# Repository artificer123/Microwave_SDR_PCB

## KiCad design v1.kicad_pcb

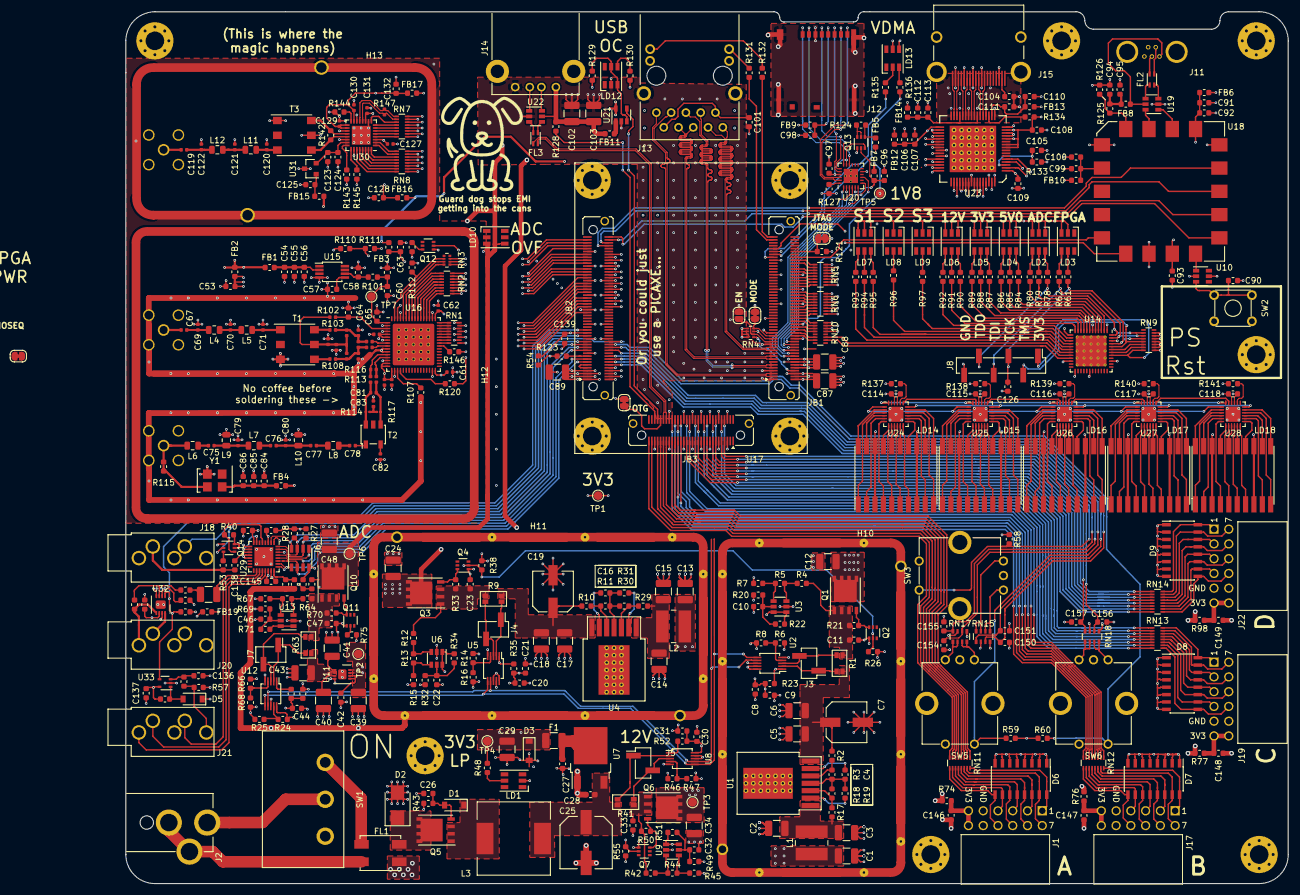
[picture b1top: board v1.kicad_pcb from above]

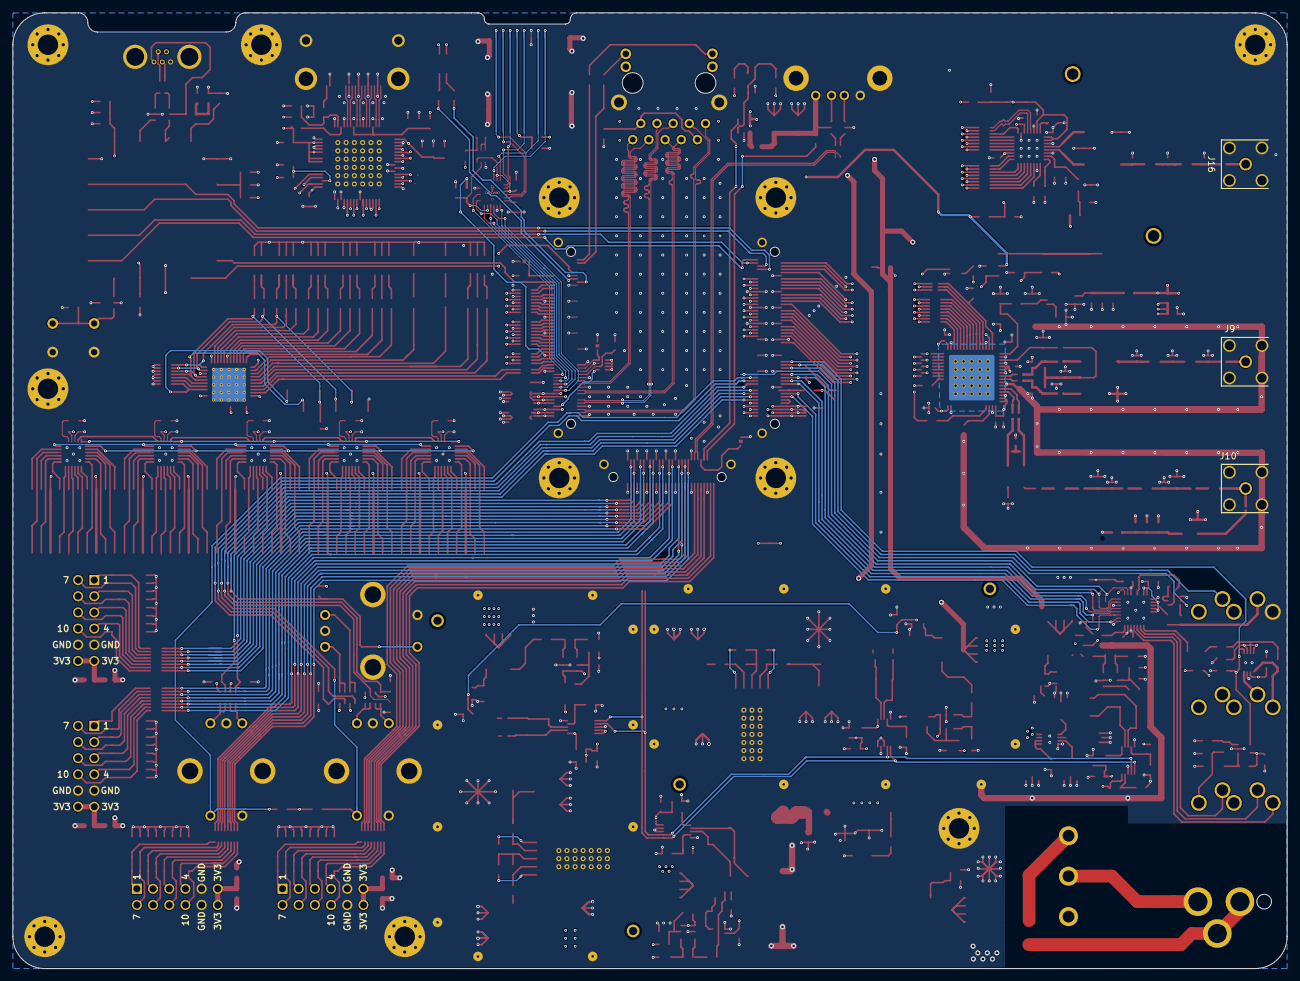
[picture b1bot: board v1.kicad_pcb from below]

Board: 4 copper layers, 200.0 x 150.0 mm, 468 parts (3 on the bottom side), 578 nets.

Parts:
C1, C2, C3, C13, C14, C15: 10u; C_1210_3225Metric
C4, C16: 470n; C_0603_1608Metric
C5, C6, C12, C17, C18, C24, C29, C34, C39, C40, C41, C43, C48, C87, C88, C89, C133: 22u; C_1210_3225Metric
C7, C19: 220u; Wurth_WCAP_PSLP
C8, C11, C20, C23, C27, C28, C30, C33, C44, C47, C136: 4u7; C_0603_1608Metric
C9, C10, C21, C22, C31, C32, C45, C46, C55, C60, C85, C90, C92, C93, C95, C100, C101, C105, C107, C108, C109, C111, C113, C114, C115, C116, C117, C118, C124, C125, C137, C139, C141, C144, C145: 100n; C_0603_1608Metric
C25: 220u; Wurth_WCAP_PSHP
C26: 47n; C_0603_1608Metric
C42, C53, C57, C63, C91, C94, C99, C123, C128, C132, C134, C142, C143, C146, C147, C148, C149, C158: 1u; C_0603_1608Metric
C50, C51, C52, C61, C62, C67, C73, C78, C82, C83, C119, C127, C129, C130, C131: 100n; C_0402_1005Metric
C54, C58, C59, C84, C106, C110, C112, C138, C140: 10u; C_0603_1608Metric
C56, C65, C86: 1n; C_0603_1608Metric
C64: 2u2; C_0603_1608Metric
C66, C72, C74, C76, C81: 8p2; C_0402_1005Metric
C68: 10n; C_0402_1005Metric
C69, C71, C120, C122: 47p; C_0402_1005Metric
C70, C121: 150p; C_0402_1005Metric
C75, C77: 22p; C_0402_1005Metric
C79, C80: 200p; C_0402_1005Metric
C96, C97, C98, C104: 100nF; C_0603_1608Metric
C102, C103: 47u; C_1210_3225Metric
C126: 22p; C_0603_1608Metric
C150, C151, C154, C155, C156, C157: 10n; C_0603_1608Metric
D1: MM3Z15VT1G; D_SOD-123
D2: SMAJ24A; D_SMB
D3: MMSZ5V1T1G; D_SOD-123
D5: MBR0520LT1G; D_SOD-123
D6, D7, D8, D9: S16C03-8; SOIC-16_3.9x9.9mm_P1.27mm
F1: 150mA; R_1210_3225Metric
FB1, FB2, FB3, FB4, FB15, FB16, FB17, FB18, FB19: Ferrite_Bead_Small; R_0603_1608Metric
FB5, FB6, FB7, FB8, FB9, FB10, FB11: Ferrite_Bead; R_0603_1608Metric
FB12, FB13, FB14: BLM18RK601SN1D; R_0603_1608Metric
FL1: ACM7060-301-2PL-TL01; TDK_ACM7060-301-2PL-TL01
FL2, FL3: 744231091; Wurth_CM_USB_744231091
H1, H2, H3, H4, H5, H6, H9: MountingHole_Pad; MountingHole_3.2mm_M3_Pad_Via
H10, H11: Shield; Shield_Masach_MS570-10_52.7x30.7x6mm_TH
H12: Shield; Shield_Masach_MS585-10_58.2x49.4x4.7mm_SMD
H13: Shield; Shield_Masach_MS511-10_51.1x25.7x6.5mm_TH
J1, J17, J19, J22: Connector_PMOD_2x6_Host; PMOD_Wurth_613012243121_Horizontal_Host
J2: Barrel_Jack_Switch; Barrel-Jack_Cliff_FC681478_TH
J3, J4, J5, J7: Conn_01x02; PinHeader_1x02_P2.54mm_Vertical_SMD_Pin1Left
J6: CLM-104-02-F-D; Header_Samtec_CLM-104-02-F-D_2x4_1mm_SM
J8: Conn_01x06_Male; PinHeader_1x06_P2.54mm_Vertical_SMD_Pin1Left
J9, J10, J16: Conn_Coaxial; SMA_Linx_CONSMA002-L-G_Horizontal
J11: USB_B_Micro; Micro-USB_Amphenol_MUSB-K152-30_Horizontal_TH
J12: Micro_SD_Card_Det; Micro-SD_Molex_503398-1892
J13: ARJM11D7-502-AB-EW2; Connector_RJ45_Magjack_Abracon_ARJM11D7-502-AB-EW2
J14: USB_A; USB-A_Wurth_61400416021_TH_RA
J15: HDMI_A; HDMI_Wurth_685119134923_Horizontal
J18: SJ1-3535NG-PI; Jack_3.5mm_CUI_SJ1-3535NG-PI_Horizontal_CircularHoles_Pink
J20, J21: SJ1-3535NG-GR; Jack_3.5mm_CUI_SJ1-3535NG-GR_Horizontal_CircularHoles_Green
JP1, JP2, JP4, JP5: SolderJumper_2_Bridged; SolderJumper-2_P1.3mm_Bridged_RoundedPad1.0x1.5mm
JP3: SolderJumper_2_Open; SolderJumper-2_P1.3mm_Open_RoundedPad1.0x1.5mm
L1, L2: 2u2; L_Wuerth_WE-PD2-Typ-MS
L3: 100uH; Wurth_7447709101
L4, L5, L11, L12: 330n; L_0805_2012Metric
L6, L8: 220n; L_0805_2012Metric
L7: 560n; L_0805_2012Metric
L9, L10: 24n; L_0805_2012Metric
LD1, LD2, LD3, LD4, LD5, LD6, LD7, LD8, LD9, LD10, LD12, LD13: LED_Cree_CLX6E-FKC; LED_RGB_PLCC-6
LD14, LD15, LD16, LD17, LD18: ACDA02-41SURKWA-F01
M1: Logo_16mmx16mm
Q1, Q3, Q5, Q6, Q10: Si7141DP; PowerPAK_SO-8_Single
Q2, Q4, Q7, Q11, Q12, Q13, Q14: SI1539CDL-T1-GE3; SOT-363_SC-70-6
R1, R9, R41: 10m; R_Shunt_Vishay_WSK1206
R2, R18, R21, R24, R26, R30, R33, R36, R37, R38, R39, R40, R43, R50, R54, R55, R57, R70, R73, R75, R101, R111, R112, R123, R124, R126, R128, R144, R145: 10k; R_0603_1608Metric
R3: 3k16; R_0603_1608Metric
R4, R64: 330k; R_0603_1608Metric
R5, R65: 2k74; R_0603_1608Metric
R6, R14, R45, R46, R48, R61, R66, R79, R85, R88, R91, R94, R96, R97, R121, R129, R135: 33k; R_0603_1608Metric
R7, R67: 44k2; R_0603_1608Metric
R8, R16, R131, R132: 1k; R_0603_1608Metric
R10: 36k; R_0603_1608Metric
R11: 6k8; R_0603_1608Metric
R12: 430k; R_0603_1608Metric
R13: 2k26; R_0603_1608Metric
R15: 36k5; R_0603_1608Metric
R17, R29: 68k; R_0603_1608Metric
R19, R31: 0R; R_0603_1608Metric
R20, R32, R49, R69: 100R; R_0603_1608Metric
R22, R23, R34, R35, R51, R52, R71, R72: 47k; R_0603_1608Metric
R25, R62, R80, R86, R89, R92, R93, R119, R130, R136, R137, R138, R139, R140, R141: 22k; R_0603_1608Metric
R27, R28: 2k2; R_0603_1608Metric
R42: 1M2; R_0603_1608Metric
R44: 12k; R_0603_1608Metric
R47: 470; R_0603_1608Metric
R53, R143: 2k; R_0603_1608Metric
R56: 100k; R_0603_1608Metric
R58, R59, R60: 10K; R_0603_1608Metric
R63: 50m; R_Shunt_Vishay_WSK1206
R68: 680; R_0603_1608Metric
R74, R76, R77, R98: 10; R_0603_1608Metric
R78, R84, R87, R90, R95: 7k5; R_0603_1608Metric
R102, R104, R109, R113, R118: 5R1; R_0402_1005Metric
R103, R108: 10R; R_0402_1005Metric
R105, R106: 35R; R_0402_1005Metric
R107, R115, R127, R133: 0; R_0603_1608Metric
R110: 5k1; R_0603_1608Metric
R114, R117: 51R; R_0201_0603Metric
R116: 100R; R_0402_1005Metric
R120, R146: 33; R_0603_1608Metric
R125: 4k7; R_0603_1608Metric
R134: 510; R_0603_1608Metric
R142: DNF; R_0603_1608Metric
R147: 1k; R_0402_1005Metric
RN1, RN2, RN5, RN6, RN10: 33; R_Array_Convex_8x0602
RN3: 33; R_Array_Convex_4x0402
RN4: 33k; R_Array_Concave_4x0402
RN7, RN8, RN11, RN12, RN13, RN14: R_Pack08; R_Array_Convex_8x0602
RN9: 5k1; R_Array_Convex_8x0602
RN15, RN17, RN18: 10k; R_Array_Convex_4x0603
SW1: SW_SPDT; C+K_Slide_SPDT_S102031MS02Q_TH
SW2: Tactile_Switch_Generic; SW_TH_Tactile_Omron_B3F-10xx
SW3, SW5, SW6: Rotary_Encoder_Switch; Bourns_QuadratureEncoder_PEC11R-4015K-S0024
T1, T3: PWB2010L; Coilcraft_PWB
T2: Macom_ETC1-1-13; Transformer_MACOM_SM-22
TP1: 3V3; TestPoint_Pad_D1.5mm
TP2: 5V0; TestPoint_Pad_D1.5mm
TP3: V In; TestPoint_Pad_D1.5mm
TP4: 3V3 LP; TestPoint_Pad_D1.5mm
TP5: 1V8; TestPoint_Pad_D1.5mm
TP6: 3V3_ADC; TestPoint_Pad_D1.5mm
TP7: TestPoint; TestPoint_Pad_D1.5mm
U1, U4: 171050601; Wurth_171050601_TO263-7EP_EP6.4x8.54mm
U2, U5, U8, U12: MAX9612; uMAX-10_3x3mm_P0.5mm
U3, U6, U9, U13: TPS3701DDCR; SOT-23-6
U7: NCP1117-3.3_TO252; TO-252-2
U10, U19, U22: TPD2S017; SOT-23-6
U11: ADM7154; LFCSP-8-1EP_3x3mm_P0.5mm_EP1.45x1.74mm
U14: LCMXO2-640HC-4SG48C; QFN-48-1EP_7x7mm_P0.5mm_EP5.3x5.3mm_ThermalVias
U15: REF5025IDGK; MSOP-8_3x3mm_P0.65mm
U16: LTC2216; QFN-64-1EP_9x9mm_P0.5mm_EP7.15x7.15mm
U17: TE0720; Trenz_TE0720
U18: JTAG-SMT3; JTAG-SMT3-NC
U20: TXS02612; WQFN-24-1EP_4.1x4.1mm_P0.5mm_EP2.45x2.45mm
U21: TPS2051B; SOT-23-5
U23: TFP410PAP; TQFP-64-1EP_10x10mm_P0.5mm_EP5x5mm_ThermalVias
U24, U25, U26, U27, U28: TLC59281RGER; QFN-24-1EP_4x4mm_P0.5mm_EP2.6x2.6mm
U29: ADAU1361; LFCSP-32-1EP_5x5mm_P0.5mm_EP3.25x3.25mm
U30: AD9744_LFCSP; LFCSP-32-1EP_5x5mm_P0.5mm_EP3.25x3.25mm
U31: ADR280RT; SOT-23
U32: SSM2211; LFCSP-8-1EP_3x3mm_P0.5mm_EP1.45x1.74mm
U33: TLV7031DCK; SOT-353_SC-70-5
Y1: SIT5001AC-3E-33N0-80.000000X; TCXO_Sitime_SiT5001_5x3.2mm

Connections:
1V8_from_FPGA: FB7.1, TP5.1, U17.1.40
3V3ADC_I_Good: R72.2, U12.1, U14.33
3V3ADC_V_Good: R71.2, U13.1, U13.6, U14.34
3V3_I_Good: R23.2, U2.1, U14.26
3V3_LP: C8.1, C9.1, C20.1, C21.1, C29.1, C30.1, C31.1, C44.1, C45.1, D3.1, F1.1, R6.1, R14.1, R20.2, R23.1, R24.1, R32.2, R35.1, R46.1, R48.1, R49.2, R52.1, R66.1, R69.2, R72.1, RN9.10, RN9.11, RN9.12, RN9.14, RN9.15, TP4.1, U2.9, U2.10, U5.8, U5.10, U8.10, U12.10, U14.1, U14.6, U14.13, U14.22, U14.25, U14.30, U14.39, U14.46
3V3_V_Good: R22.2, U3.1, U3.6, U14.27
5V_I_Good: R35.2, U5.1, U14.28
5V_V_Good: R34.2, U6.1, U6.6, U14.29
12V_I_Good: R52.2, U8.1, U14.23
12V_V_Good: R51.2, U9.1, U9.6, U14.24
+3.3VADC: C48.1, FB1.2, FB2.1, FB15.1, FB17.1, FB18.1, FB19.1, LD10.4, Q10.5, TP6.1
+3V3: C12.1, C87.1, C88.1, C89.1, C114.1, C115.1, C116.1, C117.1, C118.1, C137.1, C142.1, FB3.1, FB5.1, FB6.1, FB9.1, FB10.1, FB12.2, FB13.2, FB14.2, FB16.1, J13.L1, J13.L3, LD13.4, LD13.5, LD14.3, LD14.8, LD14.13, LD14.18, LD15.3, LD15.8, LD15.13, LD15.18, LD16.3, LD16.8, LD16.13, LD16.18, LD17.3, LD17.8, LD17.13, LD17.18, LD18.3, LD18.8, LD18.13, LD18.18, Q1.5, R27.1, R28.1, R54.1, R58.1, R59.1, R60.1, R73.1, R74.2, R76.2, R77.2, R98.2, R121.1, R123.1, R129.1, R130.1, RN4.5, RN4.6, RN4.7, RN4.8, RN15.2, RN15.4, RN17.1, RN17.3, RN18.1, RN18.3, TP1.1, U10.5, U17.1.2, U17.1.4, U17.1.6, U17.1.10, U17.1.12, U17.1.14, U17.1.16, U17.2.1, U17.2.2, U17.2.3, U17.2.4, U17.2.5, U17.2.6, U17.2.7, U17.2.8, U17.2.10, U24.21, U25.21, U26.21, U27.21, U28.21, U29.1, U33.5
+5V: C24.1, C39.1, Q3.5, TP2.1, U11.7, U11.8, U21.5
/AF ADC/DAC/CM: U29.7, U29.10, U29.12, U29.13
/FPGA/Connectors/D+: J14.3, U22.1
/FPGA/Connectors/D-: J14.2, U22.6
/FPGA/Connectors/USB_DBG_D+: U18.17, U19.6
/FPGA/Connectors/USB_DBG_D-: U18.16, U19.1
/FPGA/Connectors/~USB_OC: LD12.3, LD12.5, R129.2, U21.3
/FPGA/JB1/EN1: JP3.1, RN4.2, U17.1.27
/FPGA/JB1/JTAGMODE: JP1.1, R121.2, U17.1.90
/FPGA/JB1/MODE: JP4.1, RN4.4, U17.1.31
/FPGA/JB1/NOSEQ: JP2.1, RN4.1, U17.1.8
/FPGA/PMOD Connectors/PMOD A/1: D6.16, J1.1, RN11.16
/FPGA/PMOD Connectors/PMOD A/2: D6.14, J1.2, RN11.14
/FPGA/PMOD Connectors/PMOD A/3: D6.12, J1.3, RN11.12
/FPGA/PMOD Connectors/PMOD A/4: D6.10, J1.4, RN11.10
/FPGA/PMOD Connectors/PMOD A/7: D6.15, J1.7, RN11.15
/FPGA/PMOD Connectors/PMOD A/8: D6.13, J1.8, RN11.13
/FPGA/PMOD Connectors/PMOD A/9: D6.11, J1.9, RN11.11
/FPGA/PMOD Connectors/PMOD A/10: D6.9, J1.10, RN11.9
/FPGA/PMOD Connectors/PMOD B/1: D7.16, J17.1, RN12.16
/FPGA/PMOD Connectors/PMOD B/2: D7.14, J17.2, RN12.14
/FPGA/PMOD Connectors/PMOD B/3: D7.12, J17.3, RN12.12
/FPGA/PMOD Connectors/PMOD B/4: D7.10, J17.4, RN12.10
/FPGA/PMOD Connectors/PMOD B/7: D7.15, J17.7, RN12.15
/FPGA/PMOD Connectors/PMOD B/8: D7.13, J17.8, RN12.13
/FPGA/PMOD Connectors/PMOD B/9: D7.11, J17.9, RN12.11
/FPGA/PMOD Connectors/PMOD B/10: D7.9, J17.10, RN12.9
/FPGA/PMOD Connectors/PMOD C/1: D8.16, J19.1, RN13.16
/FPGA/PMOD Connectors/PMOD C/2: D8.14, J19.2, RN13.14
/FPGA/PMOD Connectors/PMOD C/3: D8.12, J19.3, RN13.12
/FPGA/PMOD Connectors/PMOD C/4: D8.10, J19.4, RN13.10
/FPGA/PMOD Connectors/PMOD C/7: D8.15, J19.7, RN13.15
/FPGA/PMOD Connectors/PMOD C/8: D8.13, J19.8, RN13.13
/FPGA/PMOD Connectors/PMOD C/9: D8.11, J19.9, RN13.11
/FPGA/PMOD Connectors/PMOD C/10: D8.9, J19.10, RN13.9
/FPGA/PMOD Connectors/PMOD D/1: D9.16, J22.1, RN14.16
/FPGA/PMOD Connectors/PMOD D/2: D9.14, J22.2, RN14.14
/FPGA/PMOD Connectors/PMOD D/3: D9.12, J22.3, RN14.12
/FPGA/PMOD Connectors/PMOD D/4: D9.10, J22.4, RN14.10
/FPGA/PMOD Connectors/PMOD D/7: D9.15, J22.7, RN14.15
/FPGA/PMOD Connectors/PMOD D/8: D9.13, J22.8, RN14.13
/FPGA/PMOD Connectors/PMOD D/9: D9.11, J22.9, RN14.11
/FPGA/PMOD Connectors/PMOD D/10: D9.9, J22.10, RN14.9
/HDMI/Active: RN10.15, U23.2
/HDMI/B0: RN10.16, U23.60
/HDMI/B1: RN6.9, U23.59
/HDMI/B2: RN6.10, U23.58
/HDMI/B3: RN6.12, U23.55
/HDMI/B4: RN6.13, U23.54
/HDMI/CK+: J15.10, U23.22
/HDMI/CK-: J15.12, U23.21
/HDMI/Clk: RN6.11, U23.57
/HDMI/G0: RN6.14, U23.51
/HDMI/G1: RN6.15, U23.50
/HDMI/G2: RN6.16, U23.47
/HDMI/G3: RN5.9, U23.46
/HDMI/G4: RN5.10, U23.45
/HDMI/G5: RN5.11, U23.44
/HDMI/HSync: RN10.14, U23.4
/HDMI/PVDD: C110.1, C111.1, FB13.1, U23.18
/HDMI/R0: RN5.12, U23.40
/HDMI/R1: RN5.13, U23.39
/HDMI/R2: RN5.14, U23.38
/HDMI/R3: RN5.15, U23.37
/HDMI/R4: RN5.16, U23.36
/HDMI/TX0+: J15.7, U23.25
/HDMI/TX0-: J15.9, U23.24
/HDMI/TX1+: J15.4, U23.28
/HDMI/TX1-: J15.6, U23.27
/HDMI/TX2+: J15.1, U23.31
/HDMI/TX2-: J15.3, U23.30
/HDMI/VREF: C105.1, R133.2, U23.3
/HDMI/VSync: RN10.13, U23.5
/Power Supply/Power Rail Management/3V3ADC_IFault: R80.1, U14.3
/Power Supply/Power Rail Management/3V3ADC_OK: R79.1, U14.2
/Power Supply/Power Rail Management/3V3ADC_VFault: J8.5, R78.1, RN9.2, U14.48
/Power Supply/Power Rail Management/3V3_IFault: R89.1, U14.10
/Power Supply/Power Rail Management/3V3_OK: R88.1, U14.9
/Power Supply/Power Rail Management/3V3_VFault: R87.1, U14.8
/Power Supply/Power Rail Management/5V_IFault: R86.1, U14.7
/Power Supply/Power Rail Management/5V_OK: R85.1, U14.5
/Power Supply/Power Rail Management/5V_VFault: R84.1, U14.4
/Power Supply/Power Rail Management/12V_IFault: R92.1, U14.14
/Power Supply/Power Rail Management/12V_OK: R91.1, U14.12
/Power Supply/Power Rail Management/12V_VFault: R90.1, U14.11
/Power Supply/Power Rail Management/FPGA_Fault: J8.4, R62.1, RN9.3, U14.47
/Power Supply/Power Rail Management/FPGA_OK: C126.1, J8.3, R61.1, RN9.4, U14.45
/Power Supply/Power Rail Management/I2C_Error: R93.1, U14.19
/Power Supply/Power Rail Management/JTAGEN: J8.1, RN9.8, U14.41
/Power Supply/Power Rail Management/UART_Error: R95.1, U14.17
/Power Supply/Stage 1 Regulators/12V Monitor/INa: R42.2, R44.1, U9.3
/Power Supply/Stage 1 Regulators/12V Monitor/INb: R44.2, R45.1, U9.4
/Power Supply/Stage 1 Regulators/12V Monitor/Sense+: J5.1, R41.3, U8.2
/Power Supply/Stage 1 Regulators/12V Monitor/Sense-: J5.2, R41.2, U8.3
/Power Supply/Stage 1 Regulators/12V Monitor/SetV: R46.2, R47.1, U8.4
/Power Supply/Stage 1 Regulators/12V Monitor/Vin: C33.1, Q6.1, Q6.2, Q6.3, R41.1, R42.1, R50.1
/Power Supply/Stage 1 Regulators/Vin: D2.1, FL1.2, Q5.5
/Power Supply/Stage 2 Regulators/3V3 Monitor/INa: R4.2, R5.1, U3.3
/Power Supply/Stage 2 Regulators/3V3 Monitor/INb: R5.2, R7.1, U3.4
/Power Supply/Stage 2 Regulators/3V3 Monitor/Sense+: J3.1, R1.3, U2.2
/Power Supply/Stage 2 Regulators/3V3 Monitor/Sense-: J3.2, R1.2, U2.3
/Power Supply/Stage 2 Regulators/3V3 Monitor/SetV: R6.2, R8.1, U2.4
/Power Supply/Stage 2 Regulators/3V3 Monitor/Vin: C11.1, Q1.1, Q1.2, Q1.3, R1.1, R4.1, R21.1
/Power Supply/Stage 2 Regulators/3V3_5A Regulator/FB: R2.2, R3.1, U1.5
/Power Supply/Stage 2 Regulators/3V3_5A Regulator/FB_Gnd: C4.2, R3.2, R18.2, R19.2, U1.4
/Power Supply/Stage 2 Regulators/3V3_5A Regulator/Vout: C5.1, C6.1, C7.1, R1.4, R2.1, U1.7
/Power Supply/Stage 2 Regulators/5V Monitor/INa: R12.2, R13.1, U6.3
/Power Supply/Stage 2 Regulators/5V Monitor/INb: R13.2, R15.1, U6.4
/Power Supply/Stage 2 Regulators/5V Monitor/Sense+: J4.1, R9.3, U5.2
/Power Supply/Stage 2 Regulators/5V Monitor/Sense-: J4.2, R9.2, U5.3
/Power Supply/Stage 2 Regulators/5V Monitor/SetV: R14.2, R16.1, U5.4
/Power Supply/Stage 2 Regulators/5V Monitor/Vin: C23.1, Q3.1, Q3.2, Q3.3, R9.1, R12.1, R33.1
/Power Supply/Stage 2 Regulators/5V_5A Regulator/FB: R10.2, R11.1, U4.5
/Power Supply/Stage 2 Regulators/5V_5A Regulator/FB_Gnd: C16.2, R11.2, R30.2, R31.2, U4.4
/Power Supply/Stage 2 Regulators/5V_5A Regulator/Vout: C17.1, C18.1, C19.1, R9.4, R10.1, U4.7
/Power Supply/Stage 2 Regulators/12V_In: C1.1, C13.1, C34.1, L1.1, L2.1, Q6.5, TP3.1
/Power Supply/Stage 3 Regulators/ADC 3V3 Monitor/A0: R24.2, R25.1, U12.9
/Power Supply/Stage 3 Regulators/ADC 3V3 Monitor/INa: R64.2, R65.1, U13.3
/Power Supply/Stage 3 Regulators/ADC 3V3 Monitor/INb: R65.2, R67.1, U13.4
/Power Supply/Stage 3 Regulators/ADC 3V3 Monitor/Sense+: J7.1, R63.3, U12.2
/Power Supply/Stage 3 Regulators/ADC 3V3 Monitor/Sense-: J7.2, R63.2, U12.3
/Power Supply/Stage 3 Regulators/ADC 3V3 Monitor/SetV: R66.2, R68.1, U12.4
/Power Supply/Stage 3 Regulators/ADC 3V3 Monitor/Vin: C47.1, Q10.1, Q10.2, Q10.3, R63.1, R64.1, R70.1
/RF ADC/ADC_Dither: R120.2, U16.20
/RF DAC/Clk_N: R147.1, RN7.1, U30.13
/RF DAC/Clk_P: R147.2, RN7.2, U30.12
/User Interface/Dual Seven Segment Display 1/D1_A: LD14.17, U24.7
/User Interface/Dual Seven Segment Display 1/D1_B: LD14.16, U24.9
/User Interface/Dual Seven Segment Display 1/D1_C: LD14.4, U24.6
/User Interface/Dual Seven Segment Display 1/D1_D: LD14.2, U24.5
/User Interface/Dual Seven Segment Display 1/D1_DP: LD14.5, U24.8
/User Interface/Dual Seven Segment Display 1/D1_E: LD14.1, U24.3
/User Interface/Dual Seven Segment Display 1/D1_F: LD14.19, U24.4
/User Interface/Dual Seven Segment Display 1/D1_G: LD14.20, U24.2
/User Interface/Dual Seven Segment Display 1/D2_A: LD14.12, U24.15
/User Interface/Dual Seven Segment Display 1/D2_B: LD14.11, U24.17
/User Interface/Dual Seven Segment Display 1/D2_C: LD14.9, U24.14
/User Interface/Dual Seven Segment Display 1/D2_D: LD14.7, U24.12
/User Interface/Dual Seven Segment Display 1/D2_DP: LD14.10, U24.16
/User Interface/Dual Seven Segment Display 1/D2_E: LD14.6, U24.10
/User Interface/Dual Seven Segment Display 1/D2_F: LD14.14, U24.13
/User Interface/Dual Seven Segment Display 1/D2_G: LD14.15, U24.11
/User Interface/Dual Seven Segment Display 2/D1_A: LD15.17, U25.7
/User Interface/Dual Seven Segment Display 2/D1_B: LD15.16, U25.9
/User Interface/Dual Seven Segment Display 2/D1_C: LD15.4, U25.6
/User Interface/Dual Seven Segment Display 2/D1_D: LD15.2, U25.5
/User Interface/Dual Seven Segment Display 2/D1_DP: LD15.5, U25.8
/User Interface/Dual Seven Segment Display 2/D1_E: LD15.1, U25.3
/User Interface/Dual Seven Segment Display 2/D1_F: LD15.19, U25.4
/User Interface/Dual Seven Segment Display 2/D1_G: LD15.20, U25.2
/User Interface/Dual Seven Segment Display 2/D2_A: LD15.12, U25.15
/User Interface/Dual Seven Segment Display 2/D2_B: LD15.11, U25.17
/User Interface/Dual Seven Segment Display 2/D2_C: LD15.9, U25.14
/User Interface/Dual Seven Segment Display 2/D2_D: LD15.7, U25.12
/User Interface/Dual Seven Segment Display 2/D2_DP: LD15.10, U25.16
/User Interface/Dual Seven Segment Display 2/D2_E: LD15.6, U25.10
/User Interface/Dual Seven Segment Display 2/D2_F: LD15.14, U25.13
/User Interface/Dual Seven Segment Display 2/D2_G: LD15.15, U25.11
/User Interface/Dual Seven Segment Display 2/SIN: U24.19, U25.23
/User Interface/Dual Seven Segment Display 3/D1_A: LD16.17, U26.7
/User Interface/Dual Seven Segment Display 3/D1_B: LD16.16, U26.9
/User Interface/Dual Seven Segment Display 3/D1_C: LD16.4, U26.6
/User Interface/Dual Seven Segment Display 3/D1_D: LD16.2, U26.5
/User Interface/Dual Seven Segment Display 3/D1_DP: LD16.5, U26.8
/User Interface/Dual Seven Segment Display 3/D1_E: LD16.1, U26.3
/User Interface/Dual Seven Segment Display 3/D1_F: LD16.19, U26.4
/User Interface/Dual Seven Segment Display 3/D1_G: LD16.20, U26.2
/User Interface/Dual Seven Segment Display 3/D2_A: LD16.12, U26.15
/User Interface/Dual Seven Segment Display 3/D2_B: LD16.11, U26.17
/User Interface/Dual Seven Segment Display 3/D2_C: LD16.9, U26.14
/User Interface/Dual Seven Segment Display 3/D2_D: LD16.7, U26.12
/User Interface/Dual Seven Segment Display 3/D2_DP: LD16.10, U26.16
/User Interface/Dual Seven Segment Display 3/D2_E: LD16.6, U26.10
/User Interface/Dual Seven Segment Display 3/D2_F: LD16.14, U26.13
/User Interface/Dual Seven Segment Display 3/D2_G: LD16.15, U26.11
/User Interface/Dual Seven Segment Display 3/SIN: U25.19, U26.23
/User Interface/Dual Seven Segment Display 4/D1_A: LD17.17, U27.7
/User Interface/Dual Seven Segment Display 4/D1_B: LD17.16, U27.9
/User Interface/Dual Seven Segment Display 4/D1_C: LD17.4, U27.6
/User Interface/Dual Seven Segment Display 4/D1_D: LD17.2, U27.5
/User Interface/Dual Seven Segment Display 4/D1_DP: LD17.5, U27.8
/User Interface/Dual Seven Segment Display 4/D1_E: LD17.1, U27.3
/User Interface/Dual Seven Segment Display 4/D1_F: LD17.19, U27.4
/User Interface/Dual Seven Segment Display 4/D1_G: LD17.20, U27.2
/User Interface/Dual Seven Segment Display 4/D2_A: LD17.12, U27.15
/User Interface/Dual Seven Segment Display 4/D2_B: LD17.11, U27.17
/User Interface/Dual Seven Segment Display 4/D2_C: LD17.9, U27.14
/User Interface/Dual Seven Segment Display 4/D2_D: LD17.7, U27.12
/User Interface/Dual Seven Segment Display 4/D2_DP: LD17.10, U27.16
/User Interface/Dual Seven Segment Display 4/D2_E: LD17.6, U27.10
/User Interface/Dual Seven Segment Display 4/D2_F: LD17.14, U27.13
/User Interface/Dual Seven Segment Display 4/D2_G: LD17.15, U27.11
/User Interface/Dual Seven Segment Display 4/SIN: U26.19, U27.23
/User Interface/Dual Seven Segment Display 5/D1_A: LD18.17, U28.7
/User Interface/Dual Seven Segment Display 5/D1_B: LD18.16, U28.9
/User Interface/Dual Seven Segment Display 5/D1_C: LD18.4, U28.6
/User Interface/Dual Seven Segment Display 5/D1_D: LD18.2, U28.5
/User Interface/Dual Seven Segment Display 5/D1_DP: LD18.5, U28.8
/User Interface/Dual Seven Segment Display 5/D1_E: LD18.1, U28.3
/User Interface/Dual Seven Segment Display 5/D1_F: LD18.19, U28.4
/User Interface/Dual Seven Segment Display 5/D1_G: LD18.20, U28.2
/User Interface/Dual Seven Segment Display 5/D2_A: LD18.12, U28.15
/User Interface/Dual Seven Segment Display 5/D2_B: LD18.11, U28.17
/User Interface/Dual Seven Segment Display 5/D2_C: LD18.9, U28.14
/User Interface/Dual Seven Segment Display 5/D2_D: LD18.7, U28.12
/User Interface/Dual Seven Segment Display 5/D2_DP: LD18.10, U28.16
/User Interface/Dual Seven Segment Display 5/D2_E: LD18.6, U28.10
/User Interface/Dual Seven Segment Display 5/D2_F: LD18.14, U28.13
/User Interface/Dual Seven Segment Display 5/D2_G: LD18.15, U28.11
/User Interface/Dual Seven Segment Display 5/SIN: U27.19, U28.23
ACOM: C1.2, C2.2, C3.2, C5.2, C6.2, C7.2, C8.2, C9.2, C10.2, C11.2, C12.2, C13.2, C14.2, C15.2, C17.2, C18.2, C19.2, C20.2, C21.2, C22.2, C23.2, C24.2, C25.2, C26.2, C27.2, C28.2, C29.2, C30.2, C31.2, C32.2, C33.2, C34.2, C39.2, C40.2, C41.2, C42.2, C43.2, C44.2, C45.2, C46.2, C47.2, C48.2, C50.2, C51.2, C52.2, C53.2, C54.2, C55.2, C56.2, C57.2, C58.2, C59.2, C60.2, C61.2, C62.2, C63.2, C64.2, C65.2, C66.2, C68.1, C69.2, C70.2, C71.2, C73.2, C74.2, C79.2, C80.2, C82.2, C83.2, C84.2, C85.2, C86.2, C87.2, C88.2, C89.2, C90.2, C91.2, C92.2, C93.2, C94.2, C95.2, C96.2, C97.2, C98.2, C99.2, C100.2, C101.2, C102.2, C103.2, C104.2, C105.2, C106.2, C107.2, C108.2, C109.2, C110.2, C111.2, C112.2, C113.2, C114.2, C115.2, C116.2, C117.2, C118.2, C120.2, C121.2, C122.2, C123.2, C124.2, C125.2, C126.2, C127.2, C128.2, C129.2, C130.2, C131.2, C132.2, C134.2, C136.2, C137.2, C139.2, C140.2, C141.2, C142.2, C143.2, C144.2, C145.2, C146.2, C147.2, C148.2, C149.2, C150.2, C151.2, C154.2, C155.2, C156.2, C157.2, C158.2, D2.2, D3.2, D5.1, D6.1, D6.2, D6.3, D6.4, D6.5, D6.6, D6.7, D6.8, D7.1, D7.2, D7.3, D7.4, D7.5, D7.6, D7.7, D7.8, D8.1, D8.2, D8.3, D8.4, D8.5, D8.6, D8.7, D8.8, D9.1, D9.2, D9.3, D9.4, D9.5, D9.6, D9.7, D9.8, FL1.4, H1.1, H2.1, H3.1, H4.1, H5.1, H6.1, H9.1, H10.1, H11.1, H12.1, H13.1, J1.5, J1.11, J6.8, J8.6, J9.2, J10.2, J11.5, J11.6, J12.6, J12.11, J13.11, J14.4, J14.5, J15.2, J15.5, J15.8, J15.11, J15.17, J15.SH, J16.2, J17.5, J17.11, J18.S, J19.5, J19.11, J22.5, J22.11, JP1.2, JP2.2, JP3.2, JP4.2, JP5.2, L9.2, L10.2, LD1.2, LD2.1, LD2.2, LD2.3, LD3.2, LD3.3, LD4.1, LD4.2, LD4.3, LD5.1, LD5.2, LD5.3, LD6.1, LD6.2, LD6.3, LD7.1, LD7.2, LD7.3, LD8.2, LD9.2, LD12.2, Q2.1, Q4.1, Q7.1, Q11.1, Q12.1, Q13.1, Q14.1, R7.2, R8.2, R15.2, R16.2, R25.2, R26.2, R38.2, R39.2, R43.2, R45.2, R47.2, R55.2, R57.2, R67.2, R68.2, R75.2, R107.1, R111.2, R112.2, R126.2, R127.2, R137.2, R138.2, R139.2, R140.2, R141.2, R143.2, R144.2, R145.2, RN9.9, RN9.13, SW2.3, SW2.4, SW3.C, SW3.S2, SW5.C, SW5.S2, SW6.C, SW6.S2, T1.3, T3.1, T3.5, U1.8, U2.5, U2.8, U3.2, U4.8, U5.5, U5.9, U6.2, U7.1, U8.5, U8.8, U8.9, U9.2, U10.2, U11.4, U11.9, U12.5, U12.8, U13.2, U14.49, U15.4, U16.2, U16.4, U16.7, U16.10, U16.11, U16.14, U16.18, U16.31, U16.50, U16.61, U16.65, U17.1.1, U17.1.7, U17.1.19, U17.1.25, U17.1.30, U17.1.33, U17.1.43, U17.1.53, U17.1.54, U17.1.63, U17.1.64, U17.1.73, U17.1.74, U17.1.83, U17.1.89, U17.2.19, U17.2.29, U17.2.30, U17.2.39, U17.2.40, U17.2.49, U17.2.50, U17.2.59, U17.2.60, U17.2.69, U17.2.70, U17.2.79, U17.2.80, U17.2.89, U17.3.5, U17.3.6, U17.3.11, U17.3.12, U17.3.17, U17.3.18, U17.3.23, U17.3.24, U17.3.29, U17.3.30, U17.3.35, U17.3.36, U17.3.45, U17.3.46, U17.3.55, U17.SH1, U17.SH2, U17.SH3, U18.1, U18.7, U18.14, U19.2, U20.2, U20.11, U20.25, U21.2, U22.2, U23.13, U23.14, U23.16, U23.17, U23.20, U23.26, U23.32, U23.34, U23.35, U23.41, U23.42, U23.43, U23.48, U23.52, U23.53, U23.56, U23.61, U23.62, U23.63, U23.64, U23.65, U24.22, U24.25, U25.22, U25.25, U26.22, U26.25, U27.22, U27.25, U28.22, U28.25, U29.3, U29.9, U29.22, U29.25, U29.30, U29.33, U30.10, U30.14, U30.19, U30.22, U30.26, U30.33, U31.3, U32.7, U32.9, U33.2, Y1.2
AF_ADC_DAT: J6.2, U17.2.15, U29.26
AF_BCLK: J6.6, U17.2.21, U29.28
AF_DAC_DAT: J6.4, U17.2.13, U29.27
AF_HP_DETECT: R39.1, U17.2.35, U32.1, U33.4
AF_LRCLK: J6.7, U17.2.23, U29.29
AF_MCLK: J6.1, U17.2.28, U29.2
AF_MIC_BIAS_EN: Q14.2, U17.2.31
AF_SCL: J6.3, R28.2, U17.2.27, U29.32
AF_SDA: J6.5, R27.2, U17.2.25, U29.31
AVDD: C129.1, C130.1, C131.1, C132.1, C143.1, C144.1, C145.1, FB17.2, FB18.2, U29.8, U29.23, U30.11, U30.15, U30.17, U30.18
DVDD: C106.1, C107.1, C108.1, C109.1, FB12.1, R133.1, R134.1, U23.1, U23.9, U23.10, U23.12, U23.15, U23.33
ENC1_A: C150.1, RN15.3, U17.2.24
ENC1_B: C151.1, RN15.1, U17.2.22
ENC1_SW: R58.2, SW3.S1, U17.2.12
ENC2_A: C154.1, RN17.2, U17.2.16
ENC2_B: C155.1, RN17.4, U17.2.14
ENC2_SW: R59.2, SW5.S1, U17.2.18
ENC3_A: C156.1, RN18.2, U17.3.7
ENC3_B: C157.1, RN18.4, U17.3.9
ENC3_SW: R60.2, SW6.S1, U17.2.26
ETH_MDI0_N: J13.2, U17.1.5
ETH_MDI0_P: J13.1, U17.1.3
ETH_MDI1_N: J13.4, U17.1.11
ETH_MDI1_P: J13.3, U17.1.9
ETH_MDI2_N: J13.8, U17.1.17
ETH_MDI2_P: J13.7, U17.1.15
ETH_MDI3_N: J13.10, U17.1.23
ETH_MDI3_P: J13.9, U17.1.21
FPGA_PWR_GOOD: RN4.3, U14.35, U17.1.29
HDMI_Active: RN10.2, U17.1.42
HDMI_B0: RN10.1, U17.1.44
HDMI_B1: RN6.8, U17.1.46
HDMI_B2: RN6.7, U17.1.48
HDMI_B3: RN6.5, U17.1.52
HDMI_B4: RN6.4, U17.1.56
HDMI_Clk: RN6.6, U17.1.50
HDMI_G0: RN6.3, U17.1.58
HDMI_G1: RN6.2, U17.1.60
HDMI_G2: RN6.1, U17.1.62
HDMI_G3: RN5.8, U17.1.66
HDMI_G4: RN5.7, U17.1.68
HDMI_G5: RN5.6, U17.1.70
HDMI_HSync: RN10.3, U17.1.38
HDMI_R0: RN5.5, U17.1.72
HDMI_R1: RN5.4, U17.1.76
HDMI_R2: RN5.3, U17.1.78
HDMI_R3: RN5.2, U17.1.82
HDMI_R4: RN5.1, U17.1.84
HDMI_VSync: RN10.4, U17.1.36
JB1.32: RN10.7, U17.1.32
JB1.34: RN10.6, U17.1.34
JTAG_TCK: U17.2.100, U18.10
JTAG_TDI: U17.2.96, U18.12
JTAG_TDO: U17.2.98, U18.11
JTAG_TMS: U17.2.94, U18.13
LED_BLANK: U24.18, U25.18, U26.18, U27.18, U28.18
LED_LAT: U24.1, U25.1, U26.1, U27.1, U28.1
LED_SCLK: U24.24, U25.24, U26.24, U27.24, U28.24
MON_SCL: RN9.6, U2.6, U5.6, U8.6, U12.6, U14.43
MON_SDA: RN9.7, U2.7, U5.7, U8.7, U12.7, U14.42
unnamed: C2.1, C3.1, L1.2, R17.1, U1.1
unnamed: C4.1, U1.6
unnamed: C10.1, R20.1, R22.1, U3.5
unnamed: C14.1, C15.1, L2.2, R29.1, U4.1
unnamed: C16.1, U4.6
unnamed: C22.1, R32.1, R34.1, U6.5
unnamed: C25.1, C28.1, L3.2, R41.4, U7.3
unnamed: C26.1, D1.2, Q5.4, R43.1
unnamed: C27.1, F1.2, U7.2
unnamed: C32.1, R49.1, R51.1, U9.5
unnamed: C40.1, U11.3
unnamed: C41.1, U11.1
unnamed: C42.1, U11.5, U11.6
unnamed: C43.1, R63.4, U11.2
unnamed: C46.1, R69.1, R71.1, U13.5
unnamed: C54.1, C55.1, C56.1, FB1.1, U15.2
unnamed: C57.1, U15.5
unnamed: C58.1, R101.2, U15.6
unnamed: C59.1, C60.1, C65.1, R101.1, TP7.1, U16.1
unnamed: C64.1, R102.1, U16.3
unnamed: C66.1, C72.1, R103.1, R104.2, R105.1
unnamed: C67.1, C69.1, L4.1
unnamed: C67.2, J9.1
unnamed: C68.2, C73.1, R102.2, R105.2, R106.1, T1.5
unnamed: C70.1, L4.2, L5.1
unnamed: C71.1, L5.2, T1.1
unnamed: C72.2, C74.1, R106.2, R108.1, R109.2
unnamed: C75.1, C79.1, L7.1, L9.1
unnamed: C75.2, L6.2
unnamed: C76.1, C77.1, C80.1, L10.1
unnamed: C76.2, L7.2
unnamed: C77.2, L8.2
unnamed: C78.1, L8.1
unnamed: C78.2, T2.1
unnamed: C81.1, R113.2, R114.1, T2.5
unnamed: C81.2, R117.2, R118.2, T2.3
unnamed: C82.1, T2.2
unnamed: C83.1, R114.2, R117.1
unnamed: C84.1, C85.1, C86.1, FB4.2, Y1.4
unnamed: C90.1, R123.2, SW2.1, SW2.2, U10.3
unnamed: C91.1, C92.1, C93.1, FB6.2, U18.8, U18.15
unnamed: C94.1, C95.1, FB8.1, R125.1
unnamed: C96.1, FB7.2, Q13.2, U20.5
unnamed: C97.1, Q13.3, U20.17, U20.21
unnamed: C98.1, FB9.2, J12.4
unnamed: C99.1, C100.1, FB10.2, U18.2
unnamed: C101.1, J13.5, J13.6
unnamed: C102.1, C103.1, FB11.2, J14.1, R128.2, U22.5
unnamed: C104.1, J15.18
unnamed: C119.1, C122.1, L12.1
unnamed: C119.2, J16.1
unnamed: C120.1, L11.2, T3.3
unnamed: C121.1, L11.1, L12.2
unnamed: C123.1, C124.1, U30.23, U31.2
unnamed: C125.1, FB15.2, U31.1
unnamed: C127.1, C128.1, FB16.2, U30.3
unnamed: C133.1, R37.2
unnamed: C133.2, U29.18
unnamed: C134.1, U32.2, U32.4
unnamed: C136.1, R56.1, U33.3
unnamed: C138.1, U29.11
unnamed: C138.2, J18.T, R53.2
unnamed: C140.1, C141.1, U29.24
unnamed: C146.1, J1.6, J1.12, R74.1
unnamed: C147.1, J17.6, J17.12, R76.1
unnamed: C148.1, J19.6, J19.12, R77.1
unnamed: C149.1, J22.6, J22.12, R98.1
unnamed: C158.1, FB19.2, U32.6
unnamed: D1.1, L3.1, Q5.1, Q5.2, Q5.3
unnamed: D5.2, R73.2, U33.1
unnamed: FB5.2, Q13.4, R124.1
unnamed: FB8.2, J11.1, U19.5
unnamed: FB11.1, U21.1
unnamed: FL1.1, SW1.1
unnamed: FL1.3, J2.2, J2.3
unnamed: FL2.1, J11.2
unnamed: FL2.2, U19.3
unnamed: FL2.3, J11.3
unnamed: FL2.4, U19.4
unnamed: FL3.2, U22.3
unnamed: FL3.4, U22.4
unnamed: J2.1, SW1.2
unnamed: J8.2, RN9.5, U14.44
unnamed: J10.1, L6.1, R115.1
unnamed: J12.1, U20.23
unnamed: J12.2, U20.22
unnamed: J12.3, U20.20
unnamed: J12.5, U20.19
unnamed: J12.7, U20.18
unnamed: J12.8, U20.16
unnamed: J13.L2, R131.1
unnamed: J13.L4, R132.1
unnamed: J20.S, R36.1, U32.5
unnamed: J20.T, U32.8
unnamed: J21.R, U29.19
unnamed: J21.S, U29.21
unnamed: J21.T, U29.20
unnamed: J21.TN, R56.2, R57.1
unnamed: LD1.5, R48.2
unnamed: LD2.4, R80.2
unnamed: LD2.5, R79.2
unnamed: LD2.6, R78.2
unnamed: LD3.4, R62.2
unnamed: LD3.5, R61.2
unnamed: LD4.4, R86.2
unnamed: LD4.5, R85.2
unnamed: LD4.6, R84.2
unnamed: LD5.4, R89.2
unnamed: LD5.5, R88.2
unnamed: LD5.6, R87.2
unnamed: LD6.4, R92.2
unnamed: LD6.5, R91.2
unnamed: LD6.6, R90.2
unnamed: LD7.4, R93.2
unnamed: LD7.5, R94.2
unnamed: LD7.6, R95.2
unnamed: LD8.5, R96.2
unnamed: LD9.5, R97.2
unnamed: LD10.3, R119.1
unnamed: LD12.4, R130.2
unnamed: LD13.2, R135.1
unnamed: LD13.3, R136.1
unnamed: Q1.4, Q2.6, R21.2
unnamed: Q3.4, Q4.6, R33.2
unnamed: Q6.4, Q7.6, R50.2
unnamed: Q10.4, Q11.6, R70.2
unnamed: Q12.6, R119.2
unnamed: Q13.5, Q13.6, R124.2
unnamed: Q14.3, R53.1
unnamed: Q14.4, R40.1, U29.5
unnamed: Q14.5, Q14.6, R40.2
unnamed: R17.2, R18.1, U1.3
unnamed: R19.1, U1.2
unnamed: R29.2, R30.1, U4.3
unnamed: R31.1, U4.2
unnamed: R36.2, R37.1, U32.3
unnamed: R103.2, T1.6
unnamed: R104.1, U16.8
unnamed: R107.2, U16.19
unnamed: R108.2, T1.4
unnamed: R109.1, U16.9
unnamed: R110.2, R111.1, U16.62
unnamed: R112.1, RN3.2, U16.63
unnamed: R113.1, R116.1, U16.12
unnamed: R115.2, Y1.3
unnamed: R116.2, R118.1, U16.13
unnamed: R125.2, R126.1, U18.18
unnamed: R127.1, U20.24
unnamed: R134.2, U23.19
unnamed: R137.1, U24.20
unnamed: R138.1, U25.20
unnamed: R139.1, U26.20
unnamed: R140.1, U27.20
unnamed: R141.1, U28.20
unnamed: R142.1, T3.4, U30.21
unnamed: R142.2, T3.6, U30.20
unnamed: R143.1, U30.24
unnamed: R145.1, U30.25
unnamed: R146.2, U16.40
unnamed: RN1.1, U16.48
unnamed: RN1.2, U16.47
unnamed: RN1.3, U16.46
unnamed: RN1.4, U16.45
unnamed: RN1.5, U16.44
unnamed: RN1.6, U16.43
unnamed: RN1.7, U16.42
unnamed: RN1.8, U16.41
unnamed: RN2.1, U16.58
unnamed: RN2.2, U16.57
unnamed: RN2.3, U16.56
unnamed: RN2.4, U16.55
unnamed: RN2.5, U16.54
unnamed: RN2.6, U16.53
unnamed: RN2.7, U16.52
unnamed: RN2.8, U16.51
unnamed: RN3.3, U16.60
unnamed: RN3.4, U16.59
unnamed: RN7.3, U30.9
unnamed: RN7.4, U30.8
unnamed: RN7.5, U30.7
unnamed: RN7.6, U30.6
unnamed: RN7.7, U30.5
unnamed: RN7.8, U30.4
unnamed: RN8.1, U30.2
unnamed: RN8.2, U30.1
unnamed: RN8.3, U30.32
unnamed: RN8.4, U30.31
unnamed: RN8.5, U30.30
unnamed: RN8.6, U30.29
unnamed: RN8.7, U30.28
unnamed: RN8.8, U30.27
unnamed: RN15.5, RN15.6, SW3.A
unnamed: RN15.7, RN15.8, SW3.B
unnamed: RN17.5, RN17.6, SW5.B
unnamed: RN17.7, RN17.8, SW5.A
unnamed: RN18.5, RN18.6, SW6.B
unnamed: RN18.7, RN18.8, SW6.A
unnamed: U17.2.9, U17.2.11
OVDD: C61.1, C62.1, C63.1, FB3.2, U16.32, U16.49
PMOD_A1: RN11.1, U17.3.41
PMOD_A2: RN11.3, U17.3.47
PMOD_A3: RN11.5, U17.3.51
PMOD_A4: RN11.7, U17.3.57
PMOD_A7: RN11.2, U17.3.43
PMOD_A8: RN11.4, U17.3.49
PMOD_A9: RN11.6, U17.3.53
PMOD_A10: RN11.8, U17.3.59
PMOD_B1: RN12.1, U17.3.32
PMOD_B2: RN12.3, U17.3.38
PMOD_B3: RN12.5, U17.3.37
PMOD_B4: RN12.7, U17.3.42
PMOD_B7: RN12.2, U17.3.34
PMOD_B8: RN12.4, U17.3.40
PMOD_B9: RN12.6, U17.3.39
PMOD_B10: RN12.8, U17.3.44
PMOD_C1: RN13.1, U17.3.8
PMOD_C2: RN13.3, U17.3.14
PMOD_C3: RN13.5, U17.3.20
PMOD_C4: RN13.7, U17.3.26
PMOD_C7: RN13.2, U17.3.10
PMOD_C8: RN13.4, U17.3.16
PMOD_C9: RN13.6, U17.3.22
PMOD_C10: RN13.8, U17.3.28
PMOD_D1: RN14.1, U17.3.13
PMOD_D2: RN14.3, U17.3.19
PMOD_D3: RN14.5, U17.3.25
PMOD_D4: RN14.7, U17.3.31
PMOD_D7: RN14.2, U17.3.15
PMOD_D8: RN14.4, U17.3.21
PMOD_D9: RN14.6, U17.3.27
PMOD_D10: RN14.8, U17.3.33
RF_ADC_Clk_N: RN1.9, U17.2.53
RF_ADC_Clk_P: R146.1, U17.2.51
RF_ADC_D0: RN1.10, U17.2.55
RF_ADC_D1: RN1.11, U17.2.57
RF_ADC_D2: RN1.12, U17.2.61
RF_ADC_D3: RN1.13, U17.2.63
RF_ADC_D4: RN1.14, U17.2.65
RF_ADC_D5: RN1.15, U17.2.67
RF_ADC_D6: RN1.16, U17.2.71
RF_ADC_D7: RN2.9, U17.2.73
RF_ADC_D8: RN2.10, U17.2.75
RF_ADC_D9: RN2.11, U17.2.77
RF_ADC_D10: RN2.12, U17.2.81
RF_ADC_D11: RN2.13, U17.2.83
RF_ADC_D12: RN2.14, U17.2.85
RF_ADC_D13: RN2.15, U17.2.87
RF_ADC_D14: RN2.16, U17.2.91
RF_ADC_D15: RN3.5, U17.2.93
RF_ADC_Dither: R120.1, U17.2.47
RF_ADC_Overflow: Q12.2, RN3.6, U17.2.95
RF_ADC_Random: RN3.7, U17.2.97
RF_DAC_CLK_N: RN7.16, U17.2.88
RF_DAC_CLK_P: RN7.15, U17.2.86
RF_DAC_D0: RN7.14, U17.2.84
RF_DAC_D1: RN7.13, U17.2.82
RF_DAC_D2: RN7.12, U17.2.78
RF_DAC_D3: RN7.11, U17.2.76
RF_DAC_D4: RN7.10, U17.2.74
RF_DAC_D5: RN7.9, U17.2.72
RF_DAC_D6: RN8.16, U17.2.68
RF_DAC_D7: RN8.15, U17.2.66
RF_DAC_D8: RN8.14, U17.2.64
RF_DAC_D9: RN8.13, U17.2.62
RF_DAC_D10: RN8.12, U17.2.58
RF_DAC_D11: RN8.11, U17.2.56
RF_DAC_D12: RN8.10, U17.2.54
RF_DAC_D13: RN8.9, U17.2.52
RF_DAC_MODE: R144.1, U30.16
S1_PWR_ENABLE: Q7.2, R55.1, R94.1, U14.18
S2_PWR_ENABLE: Q2.2, Q4.2, R26.1, R38.1, R96.1, U14.16
S3_PWR_ENABLE: Q11.2, R75.1, R97.1, U14.15
SD_CLK: U17.1.28, U20.9
SD_CMD: U17.1.26, U20.4
SD_DAT0: U17.1.24, U20.6
SD_DAT1: U17.1.22, U20.7
SD_DAT2: U17.1.20, U20.1
SD_DAT3: U17.1.18, U20.3
TVDD: C112.1, C113.1, FB14.1, U23.23, U23.29
UART_DEBUG_FROM_FPGA: U17.1.86, U18.5
UART_DEBUG_TO_FPGA: U17.1.91, U18.6
UART_PMIC_FROM_FPGA: RN10.10, U14.21
UART_PMIC_TO_FPGA: RN10.11, U14.20
USB_OTG_D+: FL3.1, U17.3.48
USB_OTG_D-: FL3.3, U17.3.50
USB_OTG_ID: JP5.1, U17.3.52
USB_OTG_VBUS: R128.1, U17.3.56
USB_OTG_VEN: U17.3.54, U21.4
VDD: C50.1, C51.1, C52.1, C53.1, FB2.2, FB4.1, R110.1, U16.5, U16.6, U16.15, U16.16, U16.17
~ETH_Active: R132.2, U17.1.99
~ETH_Link: R131.2, U17.1.97
~PS_RESET: U10.1, U17.2.17, U18.9
~PTT: C139.1, J18.R, R54.2, U17.2.33
~VDMA_Lock: R135.2, U17.1.85
~VDMA_Underflow: R136.2, U17.1.87

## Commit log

2019-10-06 Fixed folder SNAFU (I think?)
2019-10-06 Broke it :( Added the missing files
2019-10-07 Implemented FPGA based PMIC
2019-10-07 muppet hadn't saved everything :(
2019-10-08 started layout
2019-10-15 started regulator layout
2019-10-21 most of ADC front end done
2019-10-27 started laying out ADC
2019-10-30 connected ADC to FPGA
2019-10-30 Test commit to see if Github setup is still broken
2019-10-31 more ADC faffing
2019-11-02 Finished ADC layout
2019-11-02 bit more faffing
2019-11-03 more stuff done
2019-11-04 mostly tidying up stuff that was laid out too quickly at the weekend
2019-11-07 layout getting there! :)
2019-11-10 broke many things in the name of progress. Restore point = this commit - 1
2019-11-11 so much broken :(
2019-11-13 just about finished fiddling to add the RF DAC
2019-11-16 board nearly back in sane state after adding RF DAC
2019-11-17 made it to the painful stage - 40 traces to go (plus bells and whistles need adding)
2019-11-18 started adding AF ADC/DAC
2019-11-18 layout adjusted to fit AF stuff
2019-11-19 most of AF stage implemented
2019-11-20 bit more on AF ADC
2019-11-21 end is in sight...
2019-11-22 backup before kicad upgrade
2019-11-23 pmods connected
2019-11-23 AF DAC all connected.
2019-11-24 all traces routed! will review tomorrow
2019-11-24 DRC and ERC both passing. Ready for review
2019-11-26 As sent to JLCPCB
2020-02-02 added FPGA pin numbers to some header
2020-02-26 added FPGA pin labels to schematic
